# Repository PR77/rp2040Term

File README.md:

# rp2040Term
PR2040 VT100 Terminal with Parallel TFT LCD. Work in progress!

# Warning
This design has not been compliance tested and will not be. It may cause personal damage to you or others. I take no responsibility for this. I accept no responsibility for any damage to any equipment that results from the use of this design and its components. IT IS ENTIRELY AT YOUR OWN RISK!

# Overview
The main purpose of this design was to learn about the RP2040 scanvideo library components and utilise them with a Parallel TFT LCD. Parallel meaning the interface uses HYSNC, VSYNC, DEN (currently not used), PCLK and RGB[5] signals.

I am currently using this with a Sharp LQ042 LCD with a resolution of 480x272. This works perfectly with a 8x16 Font to give a total of 60 Columns by 17 Rows.

# Appearance Breadboard Version

# Appearance PCB Version
Here is the 3D render of the general layout. Schematics, gerbers and other support files are now available. A few improvements to the PCB will be made over time, specially I want to add the RP2040 directly to the board and not use a Pi Pico. This iterration is more or less a proof of concept.

# Credits
Repos containing some great tools and resources;
- https://geoffg.net/terminal.html
- https://github.com/Memotech-Bill/pico-colour-text/tree/main
- https://github.com/RC2014Z80/picoterm
- https://github.com/TuriSc/RP2040-PWM-DMA-Audio
- https://github.com/rewtnull/amigafonts
- https://github.com/Jamesits/bin2array

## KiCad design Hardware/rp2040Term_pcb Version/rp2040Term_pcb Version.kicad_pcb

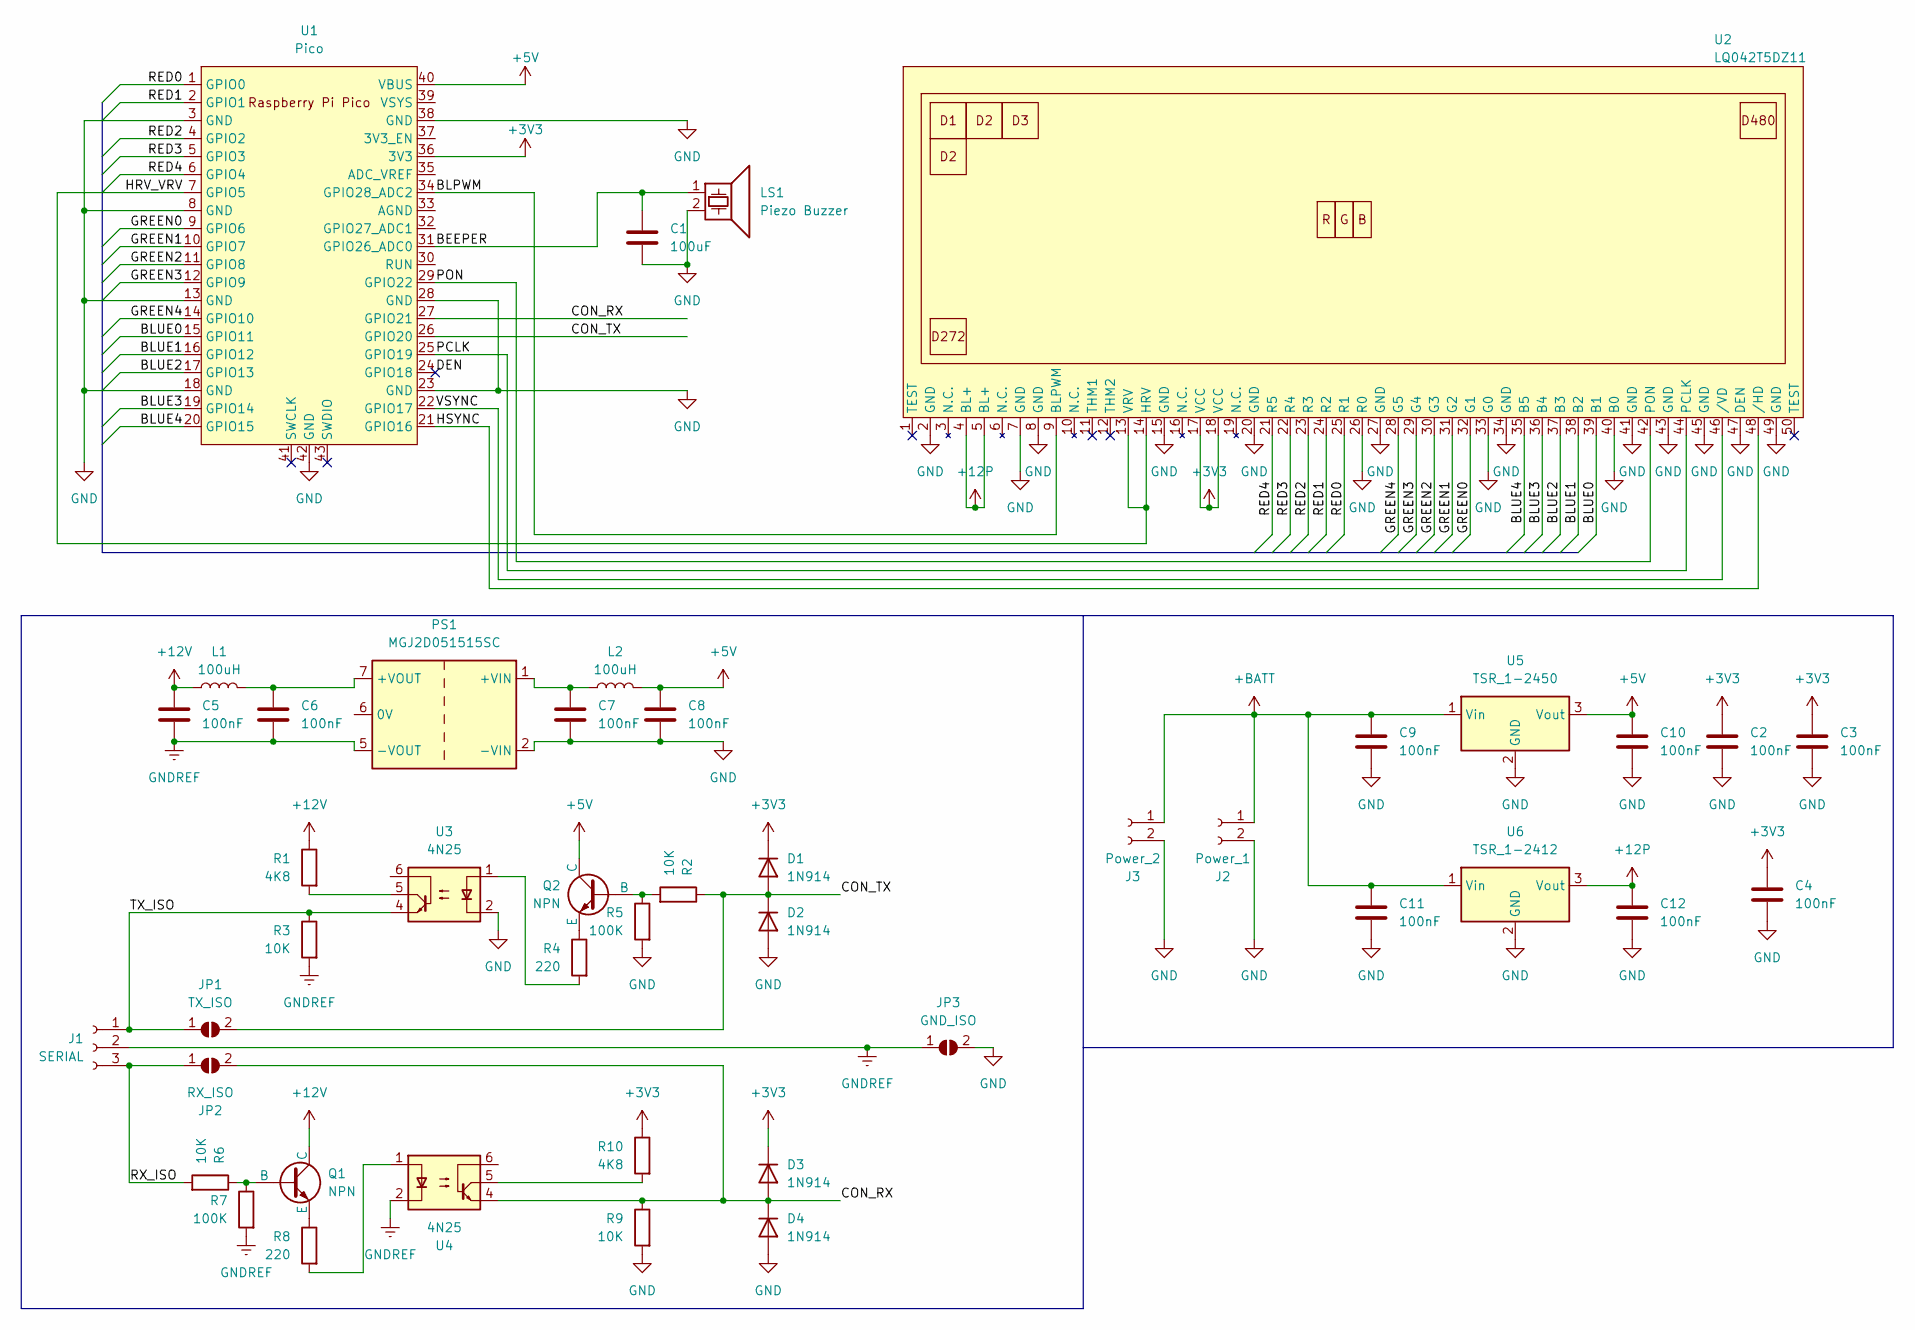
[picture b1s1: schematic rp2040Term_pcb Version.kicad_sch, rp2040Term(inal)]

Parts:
C1: 100uF; C_0805_2012Metric_Pad1.18x1.45mm_HandSolder
C2, C3, C4, C5, C6, C7, C8, C9, C10, C11, C12: 100nF; C_0805_2012Metric_Pad1.18x1.45mm_HandSolder
D1, D2, D3, D4: 1N914; D_DO-35_SOD27_P7.62mm_Horizontal
J1: SERIAL; TerminalBlock_Phoenix_MKDS-1,5-3-5.08_1x03_P5.08mm_Horizont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
J2: Power_1; PhoenixContact_MSTBA_2,5_2-G-5,08_1x02_P5.08mm_Horizontal
J3: Power_2; PhoenixContact_MSTBA_2,5_2-G-5,08_1x02_P5.08mm_Horizontal
JP1: TX_ISO; R_Axial_DIN0207_L6.3mm_D2.5mm_P10.16mm_Horizontal
JP2: RX_ISO; R_Axial_DIN0207_L6.3mm_D2.5mm_P10.16mm_Horizontal
JP3: GND_ISO; SolderJumper-2_P1.3mm_Open_TrianglePad1.0x1.5mm
L1, L2: 100uH; L_Coilcraft_XAL5050-XXX
LS1: Piezo Buzzer; Buzzer_12x9.5RM7.6
PS1: MGJ2D051515SC; Converter_DCDC_Murata_MGJ2DxxxxxxSC_THT
Q1, Q2: NPN; TO-92L_HandSolder
R1, R10: 4K8; R_0805_2012Metric_Pad1.20x1.40mm_HandSolder
R2, R3, R6, R9: 10K; R_0805_2012Metric_Pad1.20x1.40mm_HandSolder
R4, R8: 220; R_0805_2012Metric_Pad1.20x1.40mm_HandSolder
R5, R7: 100K; R_0805_2012Metric_Pad1.20x1.40mm_HandSolder
U1: Pico; RPi_Pico_SMD_TH
U2: LQ042T5DZ11; LQ042TDZ11
U3, U4: 4N25; DIP-6_W7.62mm
U5: TSR_1-2450; Converter_DCDC_TRACO_TSR-1_THT
U6: TSR_1-2412; Converter_DCDC_TRACO_TSR-1_THT

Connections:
+3V3: C2.1, C3.1, C4.1, D1.1 (K), D3.1 (K), R10.1, U1.36 (3V3), U2.17 (VCC), U2.18 (VCC)
+5V: C8.1, C10.1, L2.2, Q2.1 (C), U1.40 (VBUS), U5.3 (Vout)
+12P: C12.1, U2.4 (BL+), U2.5 (BL+), U6.3 (Vout)
+12V: C5.1, L1.1, Q1.1 (C), R1.1
+BATT: C9.1, C11.1, J2.1, J3.1, U5.1 (Vin), U6.1 (Vin)
/BEEPER: C1.1, LS1.1, U1.31 (GPIO26_ADC0)
/BLPWM: U1.34 (GPIO28_ADC2), U2.9 (BLPWM)
/BLUE0: U1.15 (GPIO11), U2.39 (B1)
/BLUE1: U1.16 (GPIO12), U2.38 (B2)
/BLUE2: U1.17 (GPIO13), U2.37 (B3)
/BLUE3: U1.19 (GPIO14), U2.36 (B4)
/BLUE4: U1.20 (GPIO15), U2.35 (B5)
/CON_RX: D3.2 (A), D4.1 (K), JP2.2 (B), R9.1, U1.27 (GPIO21), U4.4
/CON_TX: D1.2 (A), D2.1 (K), JP1.2 (B), R2.1, U1.26 (GPIO20)
/DEN: U1.24 (GPIO18)
/GREEN0: U1.9 (GPIO6), U2.32 (G1)
/GREEN1: U1.10 (GPIO7), U2.31 (G2)
/GREEN2: U1.11 (GPIO8), U2.30 (G3)
/GREEN3: U1.12 (GPIO9), U2.29 (G4)
/GREEN4: U1.14 (GPIO10), U2.28 (G5)
/HRV_VRV: U1.7 (GPIO5), U2.13 (VRV), U2.14 (HRV)
/HSYNC: U1.21 (GPIO16), U2.48 (/HD)
/PCLK: U1.25 (GPIO19), U2.44 (PCLK)
/PON: U1.29 (GPIO22), U2.42 (PON)
/RED0: U1.1 (GPIO0), U2.25 (R1)
/RED1: U1.2 (GPIO1), U2.24 (R2)
/RED2: U1.4 (GPIO2), U2.23 (R3)
/RED3: U1.5 (GPIO3), U2.22 (R4)
/RED4: U1.6 (GPIO4), U2.21 (R5)
/RX_ISO: J1.3, JP2.1 (A), R6.2
/TX_ISO: J1.1, JP1.1 (A), R3.1, U3.4
/VSYNC: U1.22 (GPIO17), U2.46 (/VD)
GND: C1.2, C2.2, C3.2, C4.2, C7.2, C8.2, C9.2, C10.2, C11.2, C12.2, D2.2 (A), D4.2 (A), J2.2, J3.2, JP3.2 (B), LS1.2, PS1.2 (-VIN), R5.2, R9.2, U1.3 (GND), U1.8 (GND), U1.13 (GND), U1.18 (GND), U1.23 (GND), U1.28 (GND), U1.38 (GND), U1.42 (GND), U2.2 (GND), U2.7 (GND), U2.8 (GND), U2.15 (GND), U2.20 (GND), U2.26 (R0), U2.27 (GND), U2.33 (G0), U2.34 (GND), U2.40 (B0), U2.41 (GND), U2.43 (GND), U2.45 (GND), U2.47 (DEN), U2.49 (GND), U2.MD, U3.2, U5.2 (GND), U6.2 (GND)
GNDREF: C5.2, C6.2, J1.2, JP3.1 (A), PS1.5 (-VOUT), R3.2, R7.2, U4.2
unnamed: C7.1, L2.1, PS1.1 (+VIN)
unnamed: C6.1, L1.2, PS1.7 (+VOUT)
unnamed: Q1.2 (B), R6.1, R7.1
unnamed: Q1.3 (E), R8.1
unnamed: Q2.2 (B), R2.2, R5.1
unnamed: Q2.3 (E), R4.1
unnamed: R1.2, U3.5
unnamed: R4.2, U3.1
unnamed: R8.2, U4.1
unnamed: R10.2, U4.5

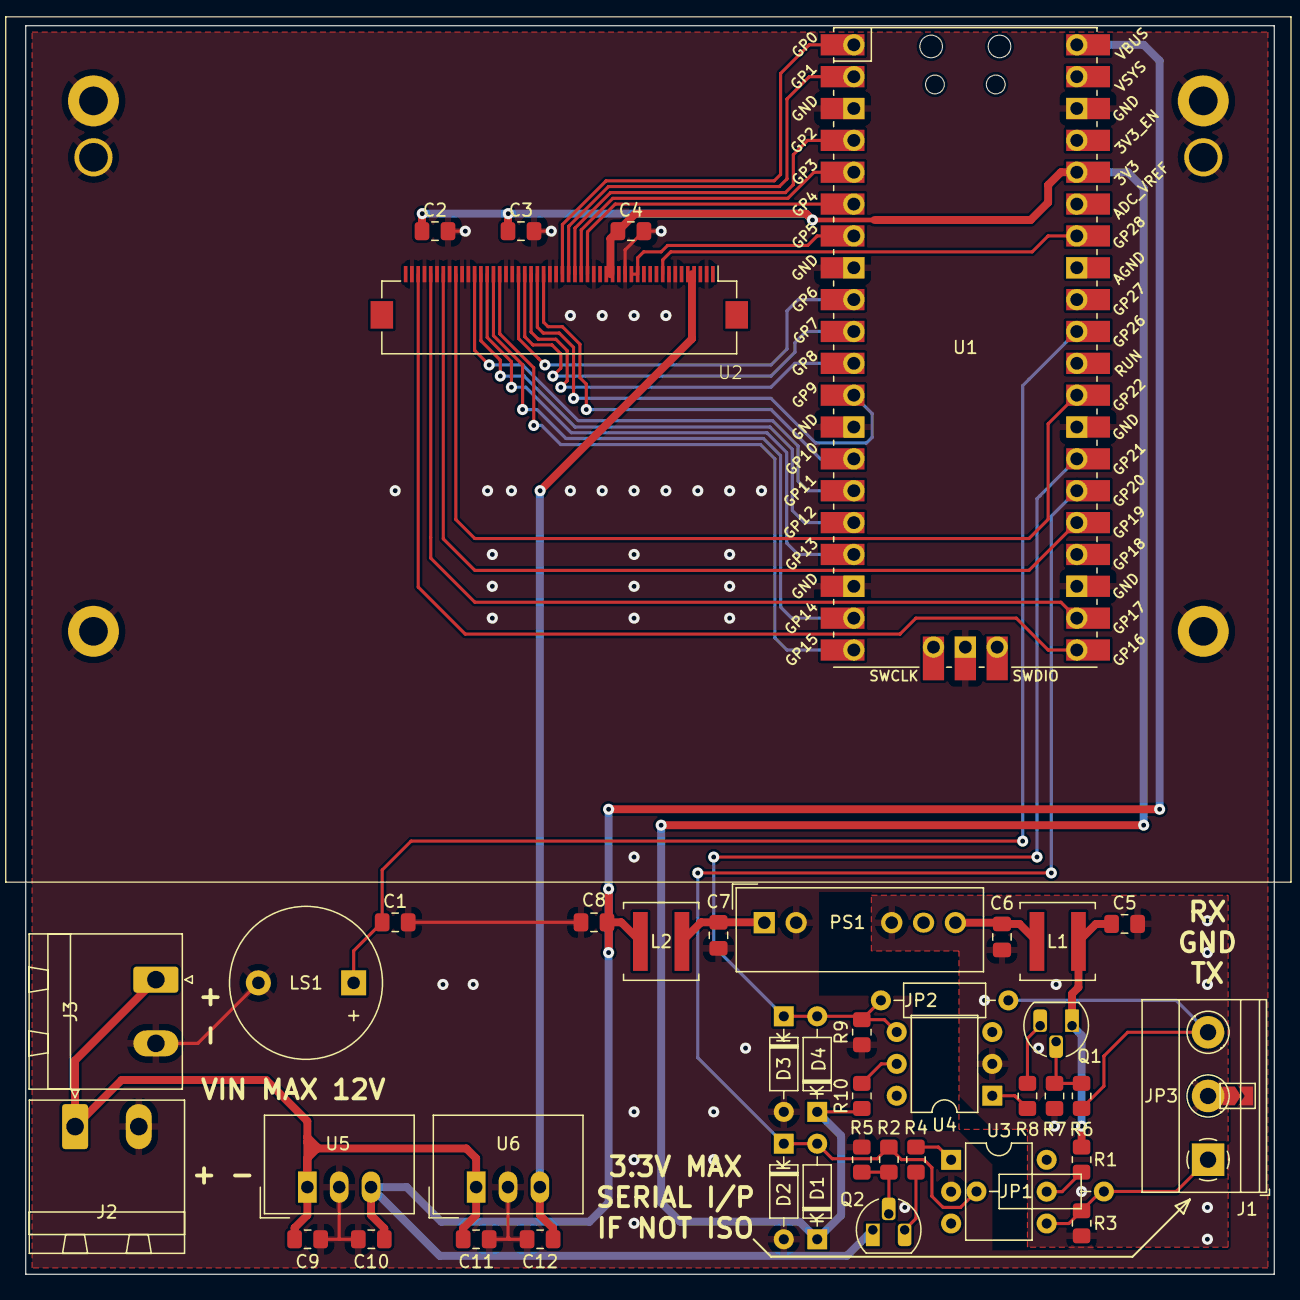
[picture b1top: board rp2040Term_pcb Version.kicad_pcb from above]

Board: 2 copper layers, 99.6 x 99.6 mm, 44 parts (0 on the bottom side), 43 nets.

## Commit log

2024-07-19 Updates
    Added support for a fixed Status Bar on the last row of the screen.
2024-07-19 Updates
    Added PWM Backlight dimming and framework for USB Keyboard support.
2024-07-19 Updates
    Added some pictures.
2024-07-21 Updates
    Auto CRLF added when cursor is at TEXT_COLUMNS_VISIBLE. Additionally, this fixes bug where first character of status bar invert attribute would be removed as the cursor would overwrite this.
2024-07-21 Updates
    Moved scanvideo timings specific for LCD out of the library components. Code cleanup.
2024-07-22 Updates
    Starting working on USB interface. Status bar now shows when USB device is connected.
2024-07-23 Updates
    Corrected keyboard layout, DE is now working.
2024-08-01 Updates
    Added support for keyboard_attachDefaultKeyHandler() and keyboard_attachCustomKeyHandler(). Made some improvements to rendering code.
2024-08-01 Updates
    Added support for key release handling.
2024-08-02 Updates
    Added support for UART transmit, CTRL-ALT-DEL system reset and more conio functions.
2024-08-02 Updates
    Support for local echo and combined key handler for conio printing and UART transmission.
2024-08-03 Updates
    Added UART receive handler interface to move conio calls out of the serial interface module. This is now mapped during initialisation / routing configuration.
2024-08-03 Updates
    Cleaned up which header files are included.
2024-08-06 Updates
    Added audio playback handler (for system Beep). Will try to link the needed audio playback repo rather than have the copy.
2024-08-07 Updates
    Cleanup folder structure.
2024-08-08 Updates
    Added control of LCD PON input.
2024-08-09 Updates
    Added HRV and VRV signals to LCD.
2024-08-12 Updates
    Added breadboard version schematic.
2024-08-12 Updates
    Added missing Piezo to schematic.
2024-08-16 Updates
    Added support for multiple fonts.
2024-08-16 Updates
    Updated credits and added fonts repo.
2024-08-16 Updates
    Renamed RP2040-PWM-DMA-Audio directory.
2024-08-16 Updates
    Fixed typo.
2024-08-20 Updates
    Added more conio handlers for cursor control, added vt100 component and additional stitching software components.
2024-08-21 Updates
    Directory structure updates.
2024-08-21 Updates
    Some cosmetic updates. Considering adding support for popups.
2024-08-22 Updates
    Update to data types and added support for simple popups.
2024-08-23 Updates
    Additional improvement to file and directory structure.
2024-08-23 Updates
    Code cleanup.
2024-08-27 Updates
    Added new font and corrected a wrong typecast.
2024-08-27 Updates
    Updated conio handler to allow printing of extended ASCII characters.
2024-08-28 Updates
    Moved CONIO_EXTENDED_ASCII_CHARACTER_SET to CMakeLists.
2024-08-28 Updates
    Backspace now also deletes the previous character.
2024-08-29 Updates
    Better conio handling.
2024-10-03 Updates
    Added pin assignment updates for PCB version.
2024-10-06 Updates
    Project description updates.
2024-10-28 Updates
    Added support for picotool pin identification.
2024-10-31 Updates
    Added PCB layout.
